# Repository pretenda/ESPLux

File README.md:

# ESPLux

This is the repo for all things ESPLux. My updates are on my webpage, [ESPLux.info](http://esplux.info).

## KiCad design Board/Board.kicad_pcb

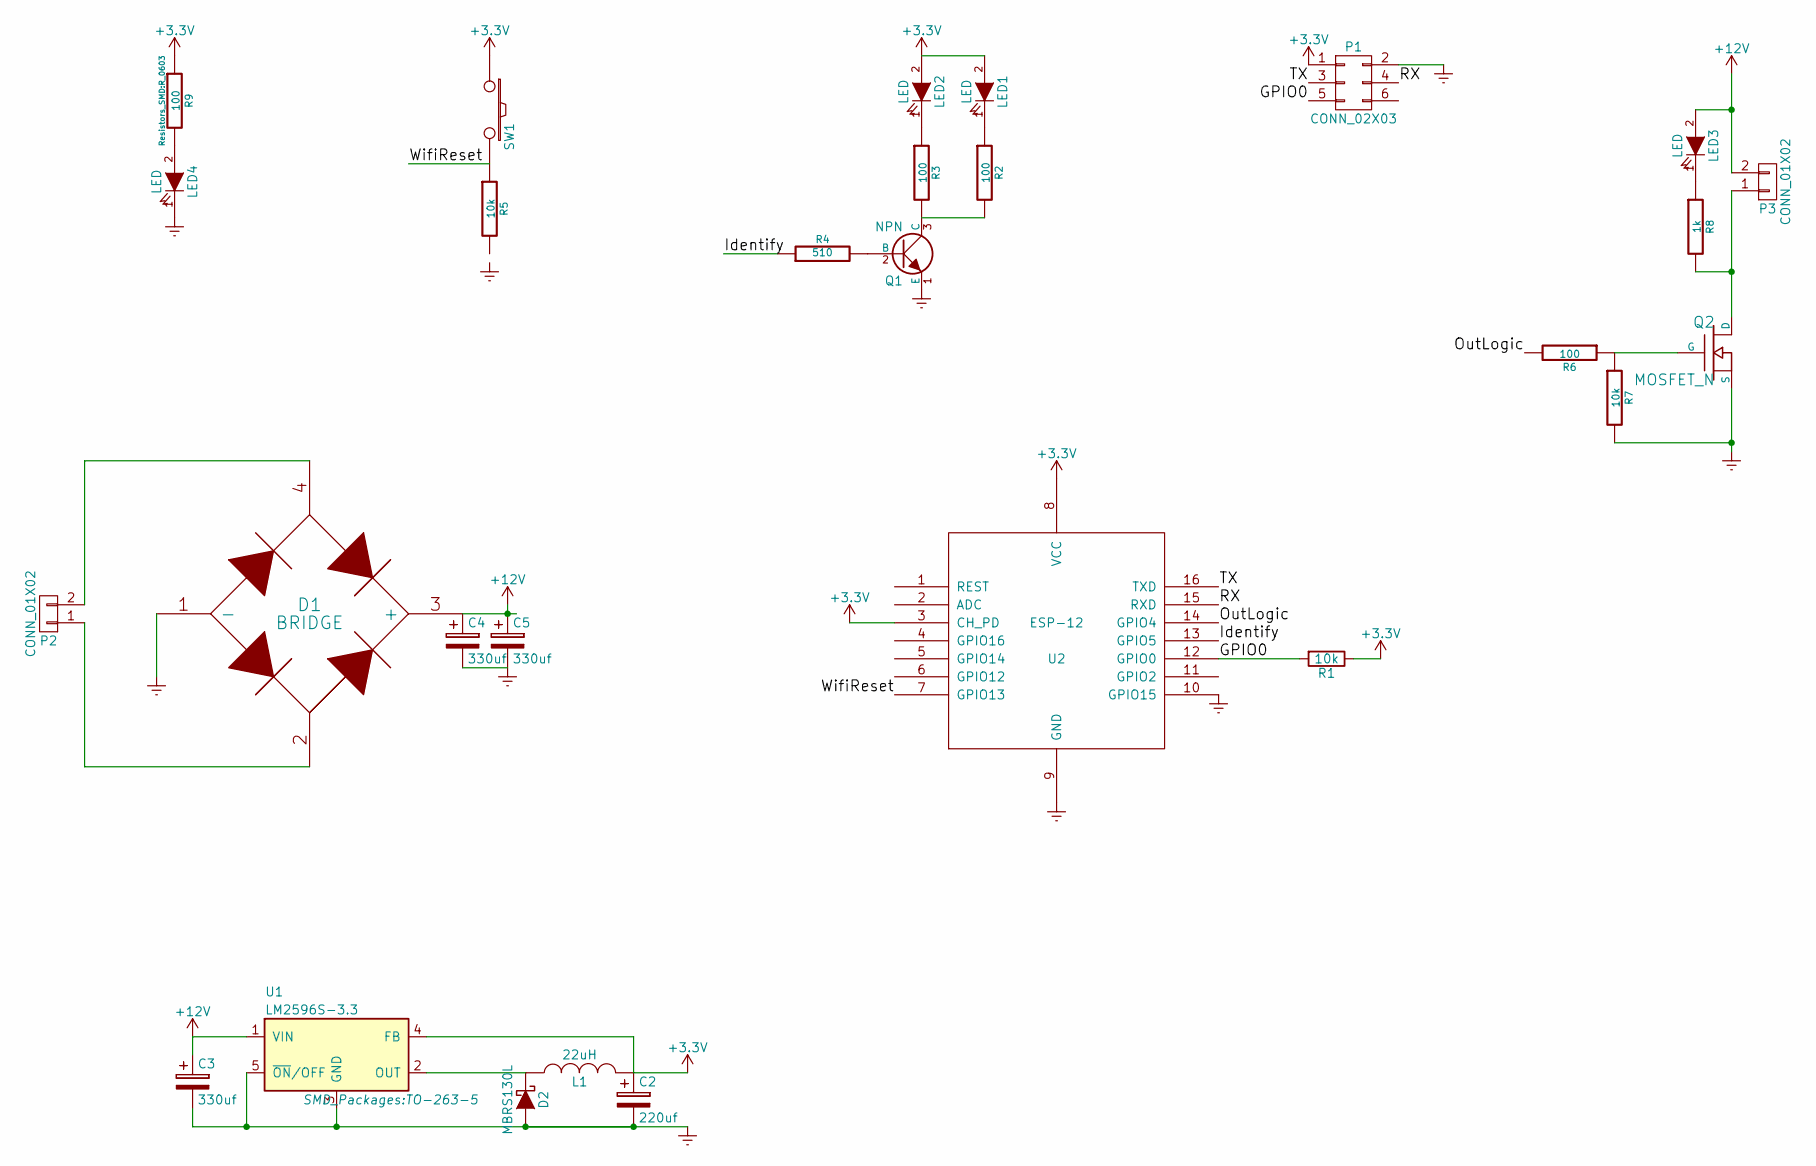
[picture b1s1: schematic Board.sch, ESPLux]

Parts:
C2: 220uf
C3, C4, C5: 330uf
D1: BRIDGE
D2: MBRS130L
L1: 22uH
LED1, LED2, LED3, LED4: LED
P1: CONN_02X03
P2, P3: CONN_01X02
Q1: NPN
Q2: MOSFET_N
R1, R7: 10k
R2, R9: 100; R_0603
R3, R6: 100
R4: 510; R_0603
R5: 10k; R_0603
R8: 1k
SW1: SW_PUSH
U1: LM2596S-3.3; TO-263-5
U2: ESP-12

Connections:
+3V3: C2.1, L1.2, LED1.2 (A), LED2.2 (A), P1.1, R1.1, R9.1, SW1.1, U1.4 (FB), U2.3 (CH_PD), U2.8 (VCC); also elsewhere on the board
+12V: C3.1, C4.1, C5.1, D1.3 (+), LED3.2 (A), P3.2, U1.1 (VIN)
/GPIO0: P1.5, R1.2, U2.12 (GPIO0)
/Identify: R4.1, U2.13 (GPIO5)
/OutLogic: R6.2, U2.14 (GPIO4)
/RX: P1.4, U2.15 (RXD)
/TX: P1.3, U2.16 (TXD)
/WifiReset: R5.1, SW1.2, U2.7 (GPIO13); also elsewhere on the board
Earth: C2.2, C3.2, C4.2, C5.2, D1.1 (-), D2.2 (A), LED4.1 (K), P1.2, Q1.1 (E), Q2.S, R7.2, U1.3 (GND), U1.5 (~ON~/OFF), U2.9 (GND), U2.10 (GPIO15)
unnamed: D1.2, P2.1
unnamed: D1.4, P2.2
unnamed: D2.1 (K), L1.1, U1.2 (OUT)
unnamed: LED1.1 (K), R2.1
unnamed: LED2.1 (K), R3.1
unnamed: LED3.1 (K), R8.1
unnamed: LED4.2 (A), R9.2
unnamed: P3.1, Q2.D, R8.2
unnamed: Q1.2 (B), R4.2
unnamed: Q1.3 (C), R2.2, R3.2
unnamed: Q2.G, R6.1, R7.1

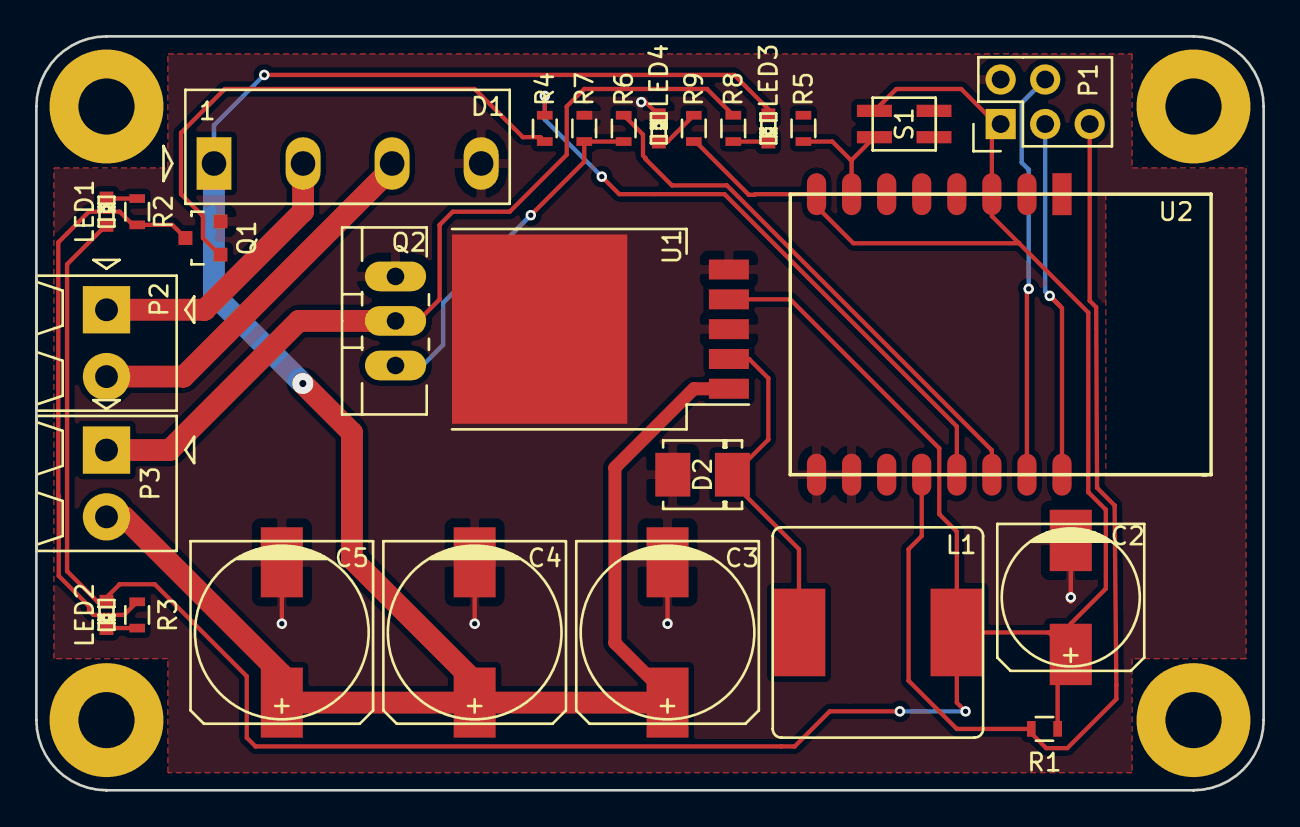
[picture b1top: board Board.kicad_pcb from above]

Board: 2 copper layers, 70.0 x 43.0 mm, 28 parts (0 on the bottom side), 20 nets.

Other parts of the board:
S1: SW_PUSH; SMD_Tact

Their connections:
+3V3: S1.1; also elsewhere on the board
/WifiReset: S1.2; also elsewhere on the board

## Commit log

2015-04-09 Case commit
2015-05-20 First pass of board added
2015-05-20 Whoops. Added the cutout on the bottom copper for the ESP8266
2015-05-21 Added a copper pour cutout for the ESP8266 and added page details
2015-05-30 First pass of web interface. No controls yet. Added first pass of case design too.
2015-05-30 Whoops. committed the wrong folder.
2015-06-03 Added link to ESPlorer
2015-06-25 All this is going .. gunna start again. Just putting it here as a backup before I do a complete rework.
2015-06-26 Basic remote control stuff ...
2015-06-29 Added license file
2015-07-10 Messy messy update. Sorry. I'll tidy it up soon.
2015-07-11 a few more changes, progressing towards a fully functional build
    a few more changes, progressing towards a fully functional build
2015-07-12 Tidy up
    Added wireless reset support with the physical button
    Added basic server storage for variables
    Added light name functionality
2015-07-12 Added the beginnings of some documentation
2015-07-15 Implemented AC on memory into init
2015-07-15 WIP of wifi and IP setup. This is currently broken, use the previous commit if you want to play
2015-07-15 Added holder for programmer (fail)
2015-07-16 Added dim on/off UI elements
2015-07-16 Case stackup for Ponoko
2015-07-16 Unable to get NodeMCU to scan for networks and list them on a webpage at this point in time. reverting.
2015-07-16 Refactor, most functionality is now working
2015-07-16 Bodged httpserver so it didnt crash when set up as an AP
2015-07-17 Added finalised case
2015-07-18 Added/updated packaging files
2015-07-23 Stripped 1k of unused code from minified file.
    In theory, it should now load 14% quicker.
2015-07-23 Fixed bug where the subnet would stop being populated after saving the light name
2015-07-27 Added beginnings of documentation
2015-07-27 Updated documentation readme
2015-07-27 *Incomplete Document!*
2015-07-27 Added documentation and photos
2015-07-28 Made light control happen earlier in the bootup sequence, light should turn on quicker now.
2015-07-28 Removed unwanted png file, updated rename file script to account for this
2015-07-28 Fixed bug where IP, Subnet and Gateway didn't hide/show properly
2015-07-29 Fixed some instances where sending the wrong command could break file writing
2015-07-29 Removed broken wait cycle on wifi reset
2015-07-31 Implemented a fix for wireless, hopefully
2015-07-31 Minor tweaks to document
2015-08-02 Added license information
2015-08-02 Updated readme, added esplorer license file
2015-08-12 Added system design diagram
2015-09-03 Updated Lid
2015-09-03 Added documentation for the HAD best product
2015-09-21 Added OpenHAB Demo
